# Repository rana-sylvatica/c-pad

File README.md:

# c-pad
simple modkit to turn GameCube controller c-stick into 4 digital directional buttons

### Overview

This repository contains the following design files:
 - 3D models of the c-pad center insert and buttons, both as individual components and panelized for ordering from a 3D printing service
 - KiCad PCB design files for both the OEM/Phob1.X and Phob2.0 versions of the project
 - PCB fabrication files (Gerber, BOM, CPL) for both the OEM/Phob1.X and Phob2.0 versions of the project

(for information about the PhobGCC project [an open-source replacement motherboard for the GameCube controller], check out https://github.com/PhobGCC)

Previously, I was selling these c-pad modkits for $30 USD on my shop at: https://ko-fi.com/ranalabs/shop

However, you can make your own for a lower price than that (especially if you make for a few friends!) using the designs posted here.

### Licensing

This project is licensed under CERN Open Hardware Licence Version 2 - Strongly Reciprocal

In short, this means:
 - License applies to publicly available hardware designs
 - Allows use, reproduction, modification, distribution, and sale of the design
 - License requires distribution under same terms, attribution to original designer(s)
 - Does not grant trademark rights, includes disclaimer of liability
 - License may be terminated for non-compliance

Anyone may use these design files to make their own c-pad for personal use or to sell, or modify the design however they wish.
However, if a modified design is distributed (either digitally or physically beyond personal use), the modified design must be publicly posted under the same terms.

Note: if selling c-pad kits, PLEASE link to this repo (or your fork of this repo, if you modify the design) on your store page.  If selling in-person, I would appreciate if it is communicated that this is an open-source project.

All these files are posted as-is. This source is distributed WITHOUT ANY EXPRESS OR IMPLIED WARRANTY, INCLUDING OF MERCHANTABILITY, SATISFACTORY QUALITY AND FITNESS FOR A PARTICULAR PURPOSE. 

### Compatibility

The c-pad design files here are split into two versions.  

One version is compatible with T3 OEM motherboards (and T1/T2 OEM motherboards with JST c-stick cables, but NOT T1/T2 that have soldered ribbon cables [different pinout]), and PhobGCC 1.X.  May also be compatible with Goomwave (untested as of yet).  This version has a 4-pin cable header on the PCB.

The other version is compatible with PhobGCC 2.0 boards.  This version has a 6-pin cable header on the PCB.

### How it works

The c-pad PCB converts digital button presses to voltage levels that correspond to appropriate analog values using a resistor network (schematic below)

The raw output from the c-pad at each of the cardinals and diagonals can be visualized with the plot below

You may note that the upper left and lower right diagonals fall well outside the unit circle.  This is not a problem, as the values are normalized by the controller to sit at the edge of the unit circle.

### Components

The following components are required to make a c-pad module:
- 1x PCB
- 1x c-pad core
- 4x c-pad button
- 1x screw (https://www.mcmaster.com/97349A413/ - there's probably other similar screws on Amazon/AliExpress/etc that would work)
- 1x ribbon cable (https://kadano.biz/phobgcc-2-0-c-stick-ribbon-cables-6pin/ - can also use individual wires but is more difficult.  If making for OEM/Phob1.X and only 6-pin ribbon cables are available, just cut off two of the wires to make a 4-pin cable)

The PCB must be ordered with SMD assembly for the resistors, capacitors, switches, and (for the Phob 2.0 version) the ADC.  I use JLCPCB for these boards.  If any components are out of stock they must be pre-ordered through JLC and received into your inventory prior to ordering the board, otherwise the board will be shipped without that component.  PCB settings: FR4 substrate, 1.6mm thickness, HASL lead free finish, SMD assembly on top side.

Resin 3D printing is the best way to manufacture the c-pad core.  Black Resin from JLCPCB (not Imagine Black - this is confusing as JLC recently added a 2nd black resin option) is my favorite for this.  Consumer-grade MSLA printers also do a nice job in my experience.

The c-pad buttons can be manufactured with resin printing, SLS/MJF nylon printing, or resin casting

SLS printing in white PA12 and dyeing with RIT dye is a nice way to get durable, vibrant, cheap buttons.  I use https://www.jawstec.com/ for this.

If ordering cores/buttons from JLC/JawsTec (or other printing service) use the panelized versions of the files for cheaper unit price (labeled as cpad_core_x4 and cpad_button_x8 in the files).  If printing the parts yourself, use the individual core/button files.

### How to assemble

Assembly is very simple:
 - put the buttons in the core
 - put together the PCB and core such that the alignment pegs line up and the slots in the core that mate with the GCC shell ribs are pointing "down" and "in" as seen from the perspective of someone holding the GCC (see image below).

### How to install

Installation is also simple:
 - desolder the existing c-stick cable from the GCC motherboard
 - solder in the new cable 
 - solder the other end of the new cable to the c-pad PCB
 - put back in shell
 - should look like the image below

### Future work?

Here are some ideas for things that would be cool to see as continuations of this project:

 - A c-pad for a Hori GCC
 - A c-pad for a Switch Pro Controller
 - Additional button(s) as angle modifiers (or a PhobGCC firmware version that reuses either X/Y as a c-pad angle modifier maybe?)
 - An improved GCC d-pad using a design similar to the c-pad
 - A version of the c-pad for the GCC left analog stick (this would be pretty silly but might be good for platformers?)

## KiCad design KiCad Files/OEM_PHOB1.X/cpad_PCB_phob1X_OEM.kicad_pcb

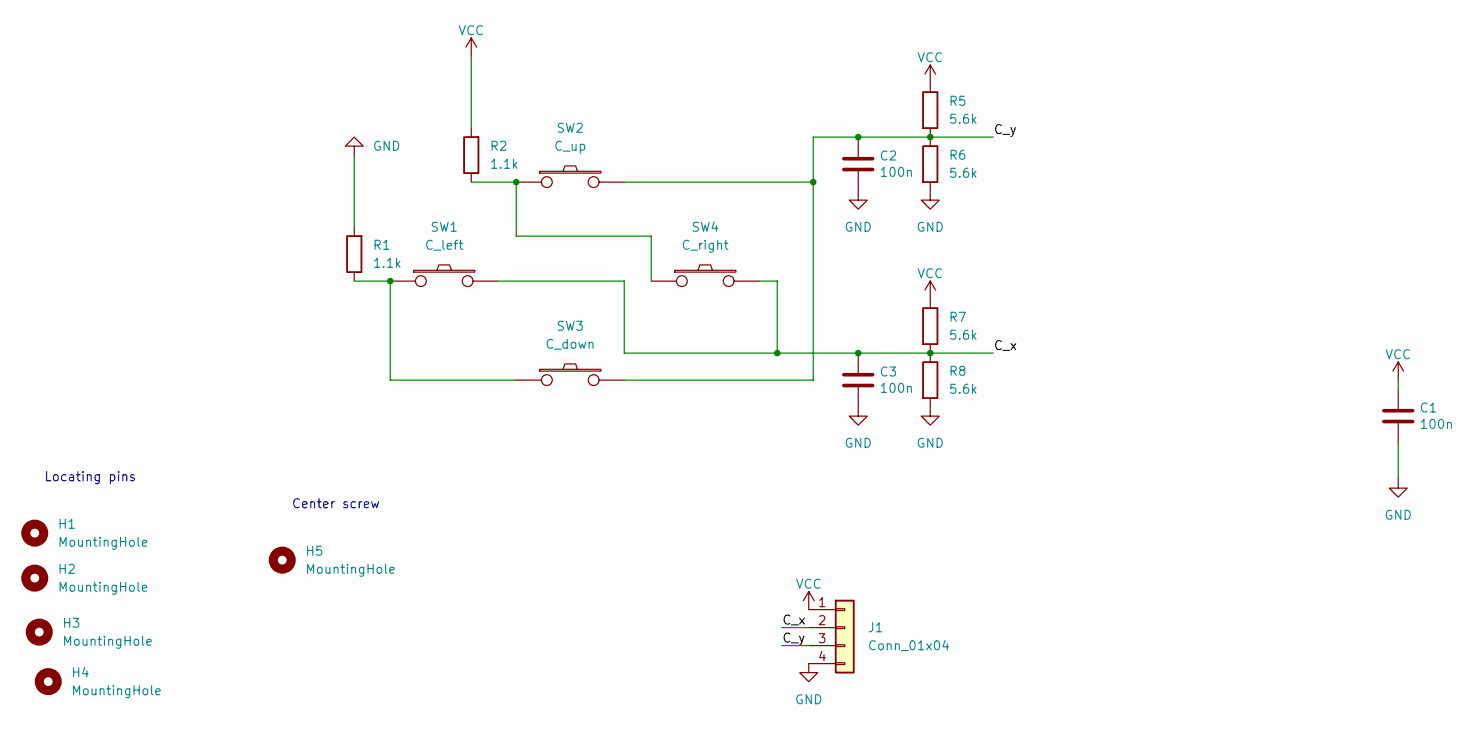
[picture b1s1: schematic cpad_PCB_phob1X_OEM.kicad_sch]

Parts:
C1, C2, C3: 100n; C_0402_1005Metric; LCSC C1525
H1, H2, H3, H4: MountingHole; MountingHole_2.1mm
H5: MountingHole; MountingHole_2.5mm
J1: Conn_01x04; PinHeader_1x04_P2.00mm_Vertical
R1, R2: 1.1k; R_0603_1608Metric_Pad0.98x0.95mm_HandSolder; LCSC C137780
R5, R6, R7, R8: 5.6k; R_0603_1608Metric_Pad0.98x0.95mm_HandSolder; LCSC C114627
SW1: C_left; SW-TH_L6.2-W6.2-P5.00; LCSC C395225
SW2: C_up; SW-TH_L6.2-W6.2-P5.00; LCSC C395225
SW3: C_down; SW-TH_L6.2-W6.2-P5.00; LCSC C395225
SW4: C_right; SW-TH_L6.2-W6.2-P5.00; LCSC C395225

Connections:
/C_x: C3.1, J1.2, R7.2, R8.1, SW1.2, SW4.2
/C_y: C2.1, J1.3, R5.2, R6.1, SW2.2, SW3.2
GND: C1.2, C2.2, C3.2, J1.4, R1.2, R6.2, R8.2
unnamed: R1.1, SW1.1, SW3.1
unnamed: R2.1, SW2.1, SW4.1
VCC: C1.1, J1.1, R2.2, R5.1, R7.1

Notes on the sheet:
Locating pins
Center screw

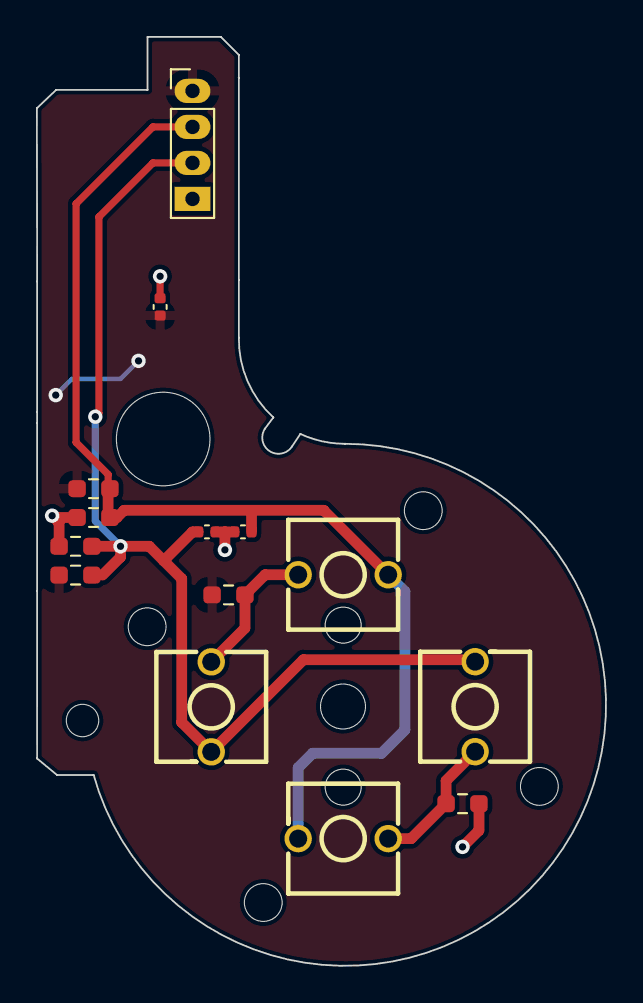
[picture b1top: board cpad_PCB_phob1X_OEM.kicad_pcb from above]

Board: 2 copper layers, 31.6 x 51.6 mm, 23 parts (0 on the bottom side), 6 nets.

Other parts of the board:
H10: MountingHole; MountingHole_1.8mm
H11: MountingHole; MountingHole_5.2mm
H12, H13: MountingHole; MountingHole_2.0mm

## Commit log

2023-04-05 Create LICENSE
2023-04-06 Add design files
2023-04-06 fix ADC rotation
